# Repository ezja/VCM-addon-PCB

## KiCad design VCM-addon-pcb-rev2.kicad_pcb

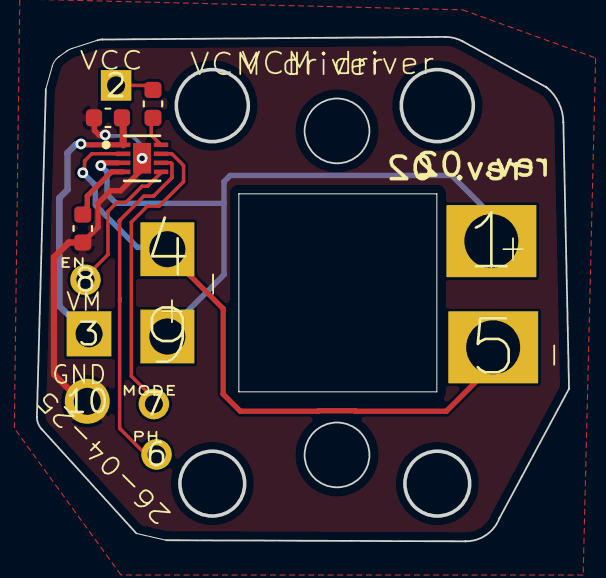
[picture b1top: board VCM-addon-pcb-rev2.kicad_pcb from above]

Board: 2 copper layers, 29.5 x 27.9 mm, 14 parts (0 on the bottom side), 9 nets.

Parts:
1, 2, 3, 4, 5, 6, 7, 8, 9, 10: (no value)
C1, C2, C3: 0.1 uF; C_0603_1608Metric
U1: DRV8210DSGR; DRV8210

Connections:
+3.3V: 2.1, C2.1
GNDREF: 10.1, C1.2, C3.1, U1.9 (Thermal_Pad)
unnamed: C1.1, U1.4 (GND)
unnamed: C2.2, U1.8 (VCC)
unnamed: 3.1, C3.2, U1.1 (VM)
PWM_EN: 8.e, U1.5 (IN2_EN)
SLEEP: 7.1, U1.7 (MODE)
VCM +: 1.e, 9.1, U1.3 (OUT2)
VCM -: 4.1, U1.2 (OUT1)

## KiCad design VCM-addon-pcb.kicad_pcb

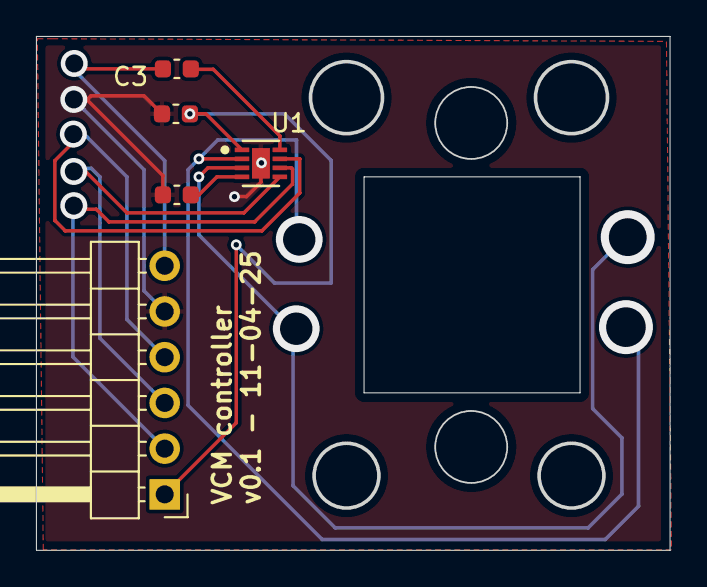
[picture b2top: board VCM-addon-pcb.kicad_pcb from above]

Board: 2 copper layers, 35.1 x 28.4 mm, 5 parts (0 on the bottom side), 8 nets.

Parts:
.54mm_Haaks: Header2.54mm_Haaks; PinHeader_1x06_P2.54mm_Horizontal
C2, C3, C4: 0.1 uF; C_0603_1608Metric
U1: DRV8210DSGR; DRV8210

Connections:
+3.3V: .54mm_Haaks.6, C3.1
GNDREF: .54mm_Haaks.5, C2.1, C4.2, U1.9 (Thermal_Pad)
unnamed: C4.1, U1.4 (GND)
unnamed: C3.2, U1.8 (VCC)
unnamed: .54mm_Haaks.1, C2.2, U1.1 (VM)
PWM_EN: .54mm_Haaks.3, U1.5 (IN2_EN)
PWM_PH: .54mm_Haaks.2, U1.6 (IN1_PH)
SLEEP: .54mm_Haaks.4, U1.7 (MODE)

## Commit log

2025-04-09 add footprint lib
2025-04-10 v0.1 schematic+pcb
2025-04-15 v0.1 correcties schroefgaten
2025-04-15 add BOM + gerber files
2025-04-15 add via to ground plane for DRV8210 thermal pad (pin 9)
2025-04-16 fixes after paper check, DRC passed + Gerber ZIP
2025-04-16 add BOM file for JLCPCB.com
2025-04-16 add drill files to Gerber zip
2025-04-16 pick & place file in JLCPCB format
2025-04-27 revision 2
